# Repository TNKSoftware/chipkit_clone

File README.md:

# chipKIT clone for PIC32MX250F128B / PIC32MX230F064B

This article introduces how to create a clone of the open source project "chipKIT" that can develop PIC32 MCUs with Arduino IDE.

"kicad" directory contains a sample circuit diagram for an USB bootloader.

"pic32mx230f" directory contains an example of developing a customized bootloader and an archived built binary for PIC32MX230F064B.

Visit my website for more details:<br>
[How to develop PIC32MX MCUs with Arduino IDE/VS Code](https://www.tnksoft.com/reading/hardware/pic32/7389.php)<br>
[How to make chipKIT clone for PIC32MX230F064B](https://www.tnksoft.com/reading/hardware/pic32/7402.php)

## :yen: Donate, please!

## :copyright: License
[Apache License 2.0](https://opensource.org/licenses/Apache-2.0)

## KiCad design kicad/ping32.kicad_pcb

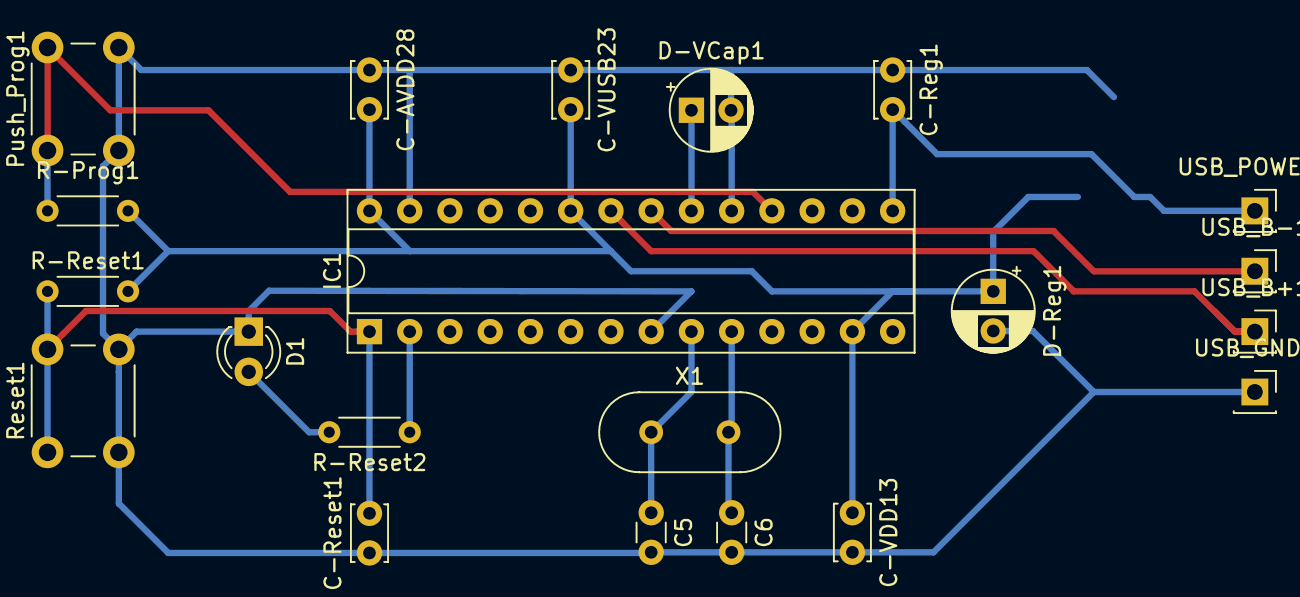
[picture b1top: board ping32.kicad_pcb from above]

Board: 2 copper layers, 22 parts (1 on the bottom side), 12 nets.

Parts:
C5, C6: 22pF; C_Disc_D3.0mm_W1.6mm_P2.50mm
C-AVDD28: 0.1uF; C_Disc_D3.4mm_W2.1mm_P2.50mm
C-Reg1: 0.1uF; C_Disc_D3.4mm_W2.1mm_P2.50mm
C-Reset1: 0.1uF; C_Disc_D3.4mm_W2.1mm_P2.50mm
C-VDD13: 0.1uF; C_Disc_D3.4mm_W2.1mm_P2.50mm
C-VUSB23: 0.1uF; C_Disc_D3.4mm_W2.1mm_P2.50mm
D1: LED_PROG; LED_D3.0mm
D-Reg1: 47uF; CP_Radial_D5.0mm_P2.50mm
D-VCap1: 10uF; CP_Radial_D5.0mm_P2.50mm
IC1: PIC32MX250F128B-I_SP; DIP-28_W7.62mm_Socket
Push_Prog1: P?; SW_PUSH_6mm_H5mm
R-Prog1: 4.7kΩ; R_Axial_DIN0204_L3.6mm_D1.6mm_P5.08mm_Horizontal
R-Reset1: 4.7kΩ; R_Axial_DIN0204_L3.6mm_D1.6mm_P5.08mm_Horizontal
R-Reset2: 330Ω; R_Axial_DIN0204_L3.6mm_D1.6mm_P5.08mm_Horizontal
Regulator1: TO252/3.3v; TO-252-2
Reset1: SW_Push; SW_PUSH_6mm_H5mm
USB_B+1: Conn_01x01; PinSocket_1x01_P2.54mm_Vertical
USB_B-1: Conn_01x01; PinSocket_1x01_P2.54mm_Vertical
USB_GND1: Conn_01x01; PinSocket_1x01_P2.54mm_Vertical
USB_POWER1: Conn_01x01; PinSocket_1x01_P2.54mm_Vertical
X1: 8MHz; Crystal_HC49-4H_Vertical

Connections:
18,SDA1,INT: IC1.18, Push_Prog1.1, R-Prog1.1
GND: C5.2, C6.2, C-AVDD28.1, C-Reg1.1, C-Reset1.1, C-VDD13.2, C-VUSB23.1, D1.1, D-Reg1.2, D-VCap1.2, IC1.8, IC1.19, IC1.27, Push_Prog1.2, Regulator1.2, Reset1.2, USB_GND1.1
unnamed: C-Reg1.2, IC1.15, Regulator1.1, USB_POWER1.1
unnamed: C-Reset1.2, IC1.1, R-Reset1.1, Reset1.1
unnamed: D1.2, R-Reset2.2
unnamed: D-VCap1.1, IC1.20
unnamed: IC1.2, R-Reset2.1
unnamed: IC1.21, USB_B-1.1
unnamed: IC1.22, USB_B+1.1
OSC1: C5.1, IC1.9, X1.1
OSC2: C6.1, IC1.10, X1.2
VDD: C-AVDD28.2, C-VDD13.1, C-VUSB23.2, D-Reg1.1, IC1.13, IC1.23, IC1.28, R-Prog1.2, R-Reset1.2, Regulator1.3

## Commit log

2020-01-12 First release
2020-01-12 Add a sample picture
2020-01-12 Add arduino exsamples
2021-01-16 Update README.md
    Update links
